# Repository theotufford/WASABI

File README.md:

# WASABI
WASABI stands for Well Applied Server Automated Biological Interface. Wasabi is a 5 bar linkage based pipetting robot that is automated via raspberry pi and the python flask library This page contains both the information and documentation for the software package as well as the mechanical assembly of the pipetting robot. The pipetting robot in this build is a slightly modified version of the [Phil pipetting robot](https://www.biorxiv.org/content/10.1101/2021.07.04.448641v1.full). Though the rpi and stepper breakout boards can be used with any machine and the wasabi machine config can be modified for any 5-bar based pipetting robot.  
## [Bill of Materials (BOM)](https://docs.google.com/spreadsheets/d/16TOlXRDoKtlOAvTiCGKz8jH9Rkvl1hXIs9z1LAUZMCc/edit?usp=sharing)

(currently working actively with this BOM but if you decide to build this project you should make your own copy and make sure to clear all of the material statuses and reset them to red so you can track)

## software outline
The core of Wasabi has three main goals:
1. intuitively program and store experiments through a visual interface 
2. run experiments and directly control the robot 

### diagram
[insert diagram here]

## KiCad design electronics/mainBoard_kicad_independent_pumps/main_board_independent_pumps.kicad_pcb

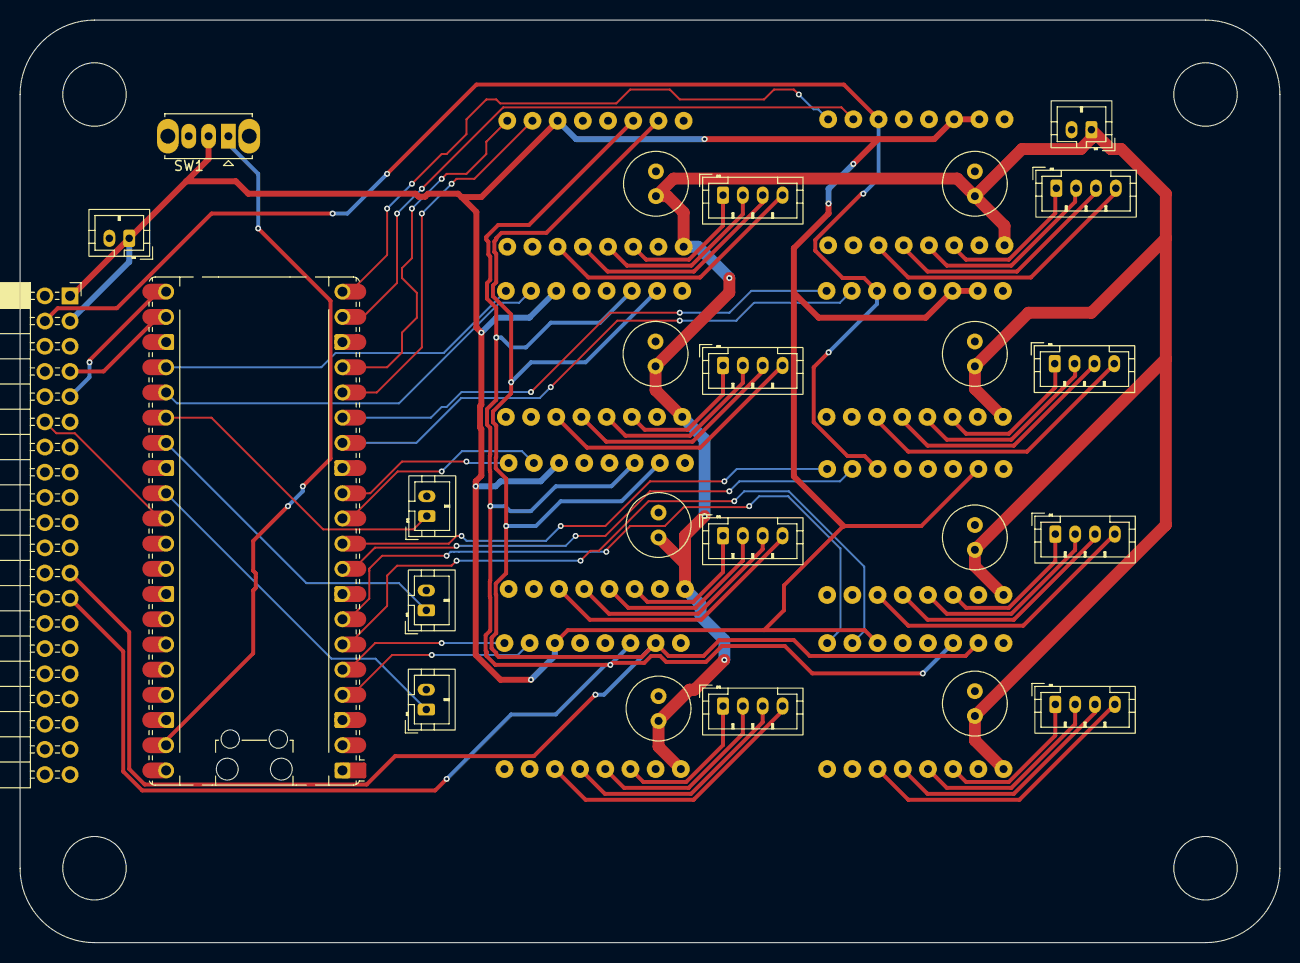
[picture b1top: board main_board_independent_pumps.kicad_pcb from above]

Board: 2 copper layers, 127.0 x 93.0 mm, 32 parts (0 on the bottom side), 61 nets.

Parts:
3b+header1: PinSocket_2x20_P2.54mm_Horizontal
A1: RaspberryPi_Pico; RaspberryPi_Pico_Common_Unspecified
A_mot1: mp6500
B_mot1: mp6500
C1, C2, C3, C4, C5, C6, C7, C8: C_Small_US; C_Radial_D6.3mm_H11.0mm_P2.50mm
J1: A_lim; JST_PH_B2B-PH-K_1x02_P2.00mm_Vertical
J2: B_lim; JST_PH_B2B-PH-K_1x02_P2.00mm_Vertical
J3: Z_lim; JST_PH_B2B-PH-K_1x02_P2.00mm_Vertical
J4, J5, J6, J7, J8, J9, J12, J13: Conn_01x04_Socket; JST_PH_B4B-PH-K_1x04_P2.00mm_Vertical
J10: 5v; JST_PH_B2B-PH-K_1x02_P2.00mm_Vertical
J11: 24v; JST_PH_B2B-PH-K_1x02_P2.00mm_Vertical
SW1: SW_DPDT_x2; SW_Slide_SPDT_Straight_CK_OS102011MS2Q
pump1, pump2, pump3, pump4, pump5: mp6500
z_mot1: mp6500

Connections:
+5V: 3b+header1.1 (5V), 3b+header1.3 (5V), A_mot1.2 (MS1), A_mot1.3 (MS2), B_mot1.2 (MS1), B_mot1.3 (MS2), J10.1, SW1.2 (B), pump1.6 (VLOG), pump2.6 (VLOG), pump3.6 (VLOG), pump4.6 (VLOG), pump5.6 (VLOG), z_mot1.2 (MS1)
+24V: A_mot1.9 (VMOT), B_mot1.9 (VMOT), C1.2, C2.2, C3.2, C4.2, C5.2, C6.2, C7.2, C8.2, J11.1, pump1.9 (VMOT), pump2.9 (VMOT), pump3.9 (VMOT), pump4.9 (VMOT), pump5.9 (VMOT), z_mot1.9 (VMOT)
/A_dir: A1.20 (GPIO15), A_mot1.8 (DIR)
/A_step: A1.19 (GPIO14), A_mot1.7 (STEP)
/B_dir: A1.15 (GPIO11), B_mot1.8 (DIR)
/B_step: A1.14 (GPIO10), B_mot1.7 (STEP)
/P_ms1: 3b+header1.23 (GPIO8), pump1.2 (MS1), pump2.2 (MS1), pump3.2 (MS1), pump4.2 (MS1), pump5.2 (MS1)
/P_ms2: 3b+header1.25 (GPIO7), pump1.3 (MS2), pump2.3 (MS2), pump3.3 (MS2), pump4.3 (MS2), pump5.3 (MS2)
/Pico_reset: 3b+header1.12 (GPIO17), A1.30 (RUN)
/enable: 3b+header1.4 (GPIO2), A_mot1.6 (VLOG), B_mot1.6 (VLOG), z_mot1.6 (VLOG)
/p1_dir: A1.7 (GPIO5), pump1.8 (DIR)
/p1_step: A1.6 (GPIO4), pump1.7 (STEP)
/p2_dir: A1.17 (GPIO13), pump2.8 (DIR)
/p2_step: A1.16 (GPIO12), pump2.7 (STEP)
/p3_dir: A1.24 (GPIO18), pump3.8 (DIR)
/p3_step: A1.25 (GPIO19), pump3.7 (STEP)
/p4_dir: A1.5 (GPIO3), pump4.8 (DIR)
/p4_step: A1.4 (GPIO2), pump4.7 (STEP)
/p5_dir: A1.12 (GPIO9), pump5.8 (DIR)
/p5_step: A1.11 (GPIO8), pump5.7 (STEP)
/uart_RX: 3b+header1.9 (GPIO15), A1.21 (GPIO16)
/uart_TX: 3b+header1.7 (GPIO14), A1.22 (GPIO17)
/z_dir: A1.10 (GPIO7), z_mot1.8 (DIR)
/z_step: A1.9 (GPIO6), z_mot1.7 (STEP)
GND: 3b+header1.5 (GND), 3b+header1.10 (GND), 3b+header1.13 (GND), 3b+header1.19 (GND), 3b+header1.26 (GND), 3b+header1.33 (GND), 3b+header1.40 (GND), A1.3 (GND), A1.8 (GND), A1.13 (GND), A1.18 (GND), A1.23 (GND), A1.28 (GND), A1.33 (AGND), A1.38 (GND), A_mot1.10 (GND), A_mot1.16 (LGND), B_mot1.10 (GND), B_mot1.16 (LGND), C1.1, C2.1, C3.1, C4.1, C5.1, C6.1, C7.1, C8.1, J1.2, J2.2, J3.2, J10.2, J11.2, pump1.10 (GND), pump1.16 (LGND), pump2.10 (GND), pump2.16 (LGND), pump3.10 (GND), pump3.16 (LGND), pump4.10 (GND), pump4.16 (LGND), pump5.10 (GND), pump5.16 (LGND), z_mot1.10 (GND), z_mot1.16 (LGND)
unnamed: A1.26 (GPIO20), J3.1
unnamed: A1.27 (GPIO21), J2.1
unnamed: A1.29 (GPIO22), J1.1
unnamed: A1.39 (VSYS), SW1.1 (A)
unnamed: A_mot1.13 (A1), J4.3
unnamed: A_mot1.14 (A2), J4.4
unnamed: A_mot1.12 (B1), J4.2
unnamed: A_mot1.11 (B2), J4.1
unnamed: B_mot1.13 (A1), J5.3
unnamed: B_mot1.14 (A2), J5.4
unnamed: B_mot1.12 (B1), J5.2
unnamed: B_mot1.11 (B2), J5.1
unnamed: J6.1, z_mot1.11 (B2)
unnamed: J6.2, z_mot1.12 (B1)
unnamed: J6.3, z_mot1.13 (A1)
unnamed: J6.4, z_mot1.14 (A2)
unnamed: J7.1, pump3.11 (B2)
unnamed: J7.2, pump3.12 (B1)
unnamed: J7.3, pump3.13 (A1)
unnamed: J7.4, pump3.14 (A2)
unnamed: J8.1, pump2.11 (B2)
unnamed: J8.2, pump2.12 (B1)
unnamed: J8.3, pump2.13 (A1)
unnamed: J8.4, pump2.14 (A2)
unnamed: J9.1, pump1.11 (B2)
unnamed: J9.2, pump1.12 (B1)
unnamed: J9.3, pump1.13 (A1)
unnamed: J9.4, pump1.14 (A2)
unnamed: J12.1, pump4.11 (B2)
unnamed: J12.2, pump4.12 (B1)
unnamed: J12.3, pump4.13 (A1)
unnamed: J12.4, pump4.14 (A2)
unnamed: J13.1, pump5.11 (B2)
unnamed: J13.2, pump5.12 (B1)
unnamed: J13.3, pump5.13 (A1)
unnamed: J13.4, pump5.14 (A2)

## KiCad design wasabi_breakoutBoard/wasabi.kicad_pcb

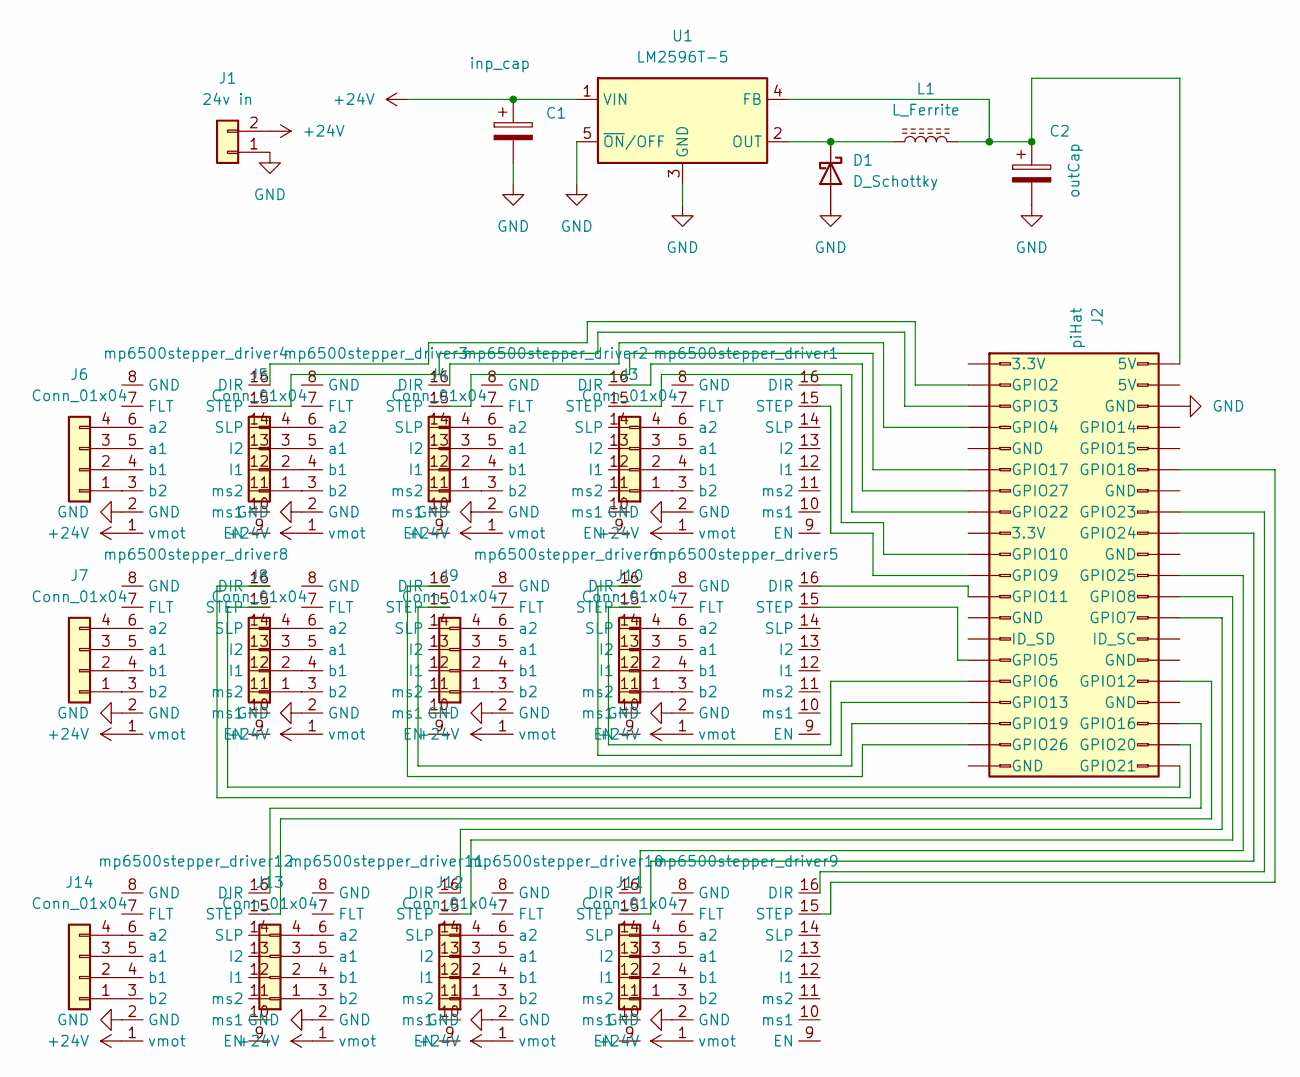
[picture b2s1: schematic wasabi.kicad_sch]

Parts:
C1: inp_cap; C_Radial_D10.0mm_H20.0mm_P5.00mm
C2: outCap; CP_Radial_D8.0mm_P3.50mm
D1: D_Schottky; D_DO-201AD_P15.24mm_Horizontal
J1: 24v in; JST_XH_B2B-XH-A_1x02_P2.50mm_Vertical
J2: piHat; PinHeader_2x20_P2.54mm_Vertical
J3, J4, J5, J6, J7, J8, J9, J10, J11, J12, J13, J14: Conn_01x04; JST_XH_B4B-XH-A_1x04_P2.50mm_Vertical
L1: L_Ferrite; L_Coilcraft_MSS1278-XXX
U1: LM2596T-5; TO-220-5_P3.4x3.7mm_StaggerOdd_Lead3.8mm_Vertical
mp6500stepper_driver1, mp6500stepper_driver2, mp6500stepper_driver3, mp6500stepper_driver4, mp6500stepper_driver5, mp6500stepper_driver6, mp6500stepper_driver7, mp6500stepper_driver8, mp6500stepper_driver9, mp6500stepper_driver10, mp6500stepper_driver11, mp6500stepper_driver12: mp6500

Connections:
+24V: C1.1, J1.2, U1.1 (VIN), mp6500stepper_driver1.1 (vmot), mp6500stepper_driver2.1 (vmot), mp6500stepper_driver3.1 (vmot), mp6500stepper_driver4.1 (vmot), mp6500stepper_driver5.1 (vmot), mp6500stepper_driver6.1 (vmot), mp6500stepper_driver7.1 (vmot), mp6500stepper_driver8.1 (vmot), mp6500stepper_driver9.1 (vmot), mp6500stepper_driver10.1 (vmot), mp6500stepper_driver11.1 (vmot), mp6500stepper_driver12.1 (vmot)
GND: C1.2, C2.2, D1.2 (A), J1.1, J2.6 (GND), U1.3 (GND), U1.5 (~ON/OFF), mp6500stepper_driver1.2 (GND), mp6500stepper_driver2.2 (GND), mp6500stepper_driver3.2 (GND), mp6500stepper_driver4.2 (GND), mp6500stepper_driver5.2 (GND), mp6500stepper_driver6.2 (GND), mp6500stepper_driver7.2 (GND), mp6500stepper_driver8.2 (GND), mp6500stepper_driver9.2 (GND), mp6500stepper_driver10.2 (GND), mp6500stepper_driver11.2 (GND), mp6500stepper_driver12.2 (GND)
unnamed: D1.1 (K), L1.1, U1.2 (OUT)
unnamed: J2.3 (GPIO2), mp6500stepper_driver4.16 (DIR)
unnamed: J2.5 (GPIO3), mp6500stepper_driver4.15 (STEP)
unnamed: J2.7 (GPIO4), mp6500stepper_driver3.16 (DIR)
unnamed: J2.29 (GPIO5), mp6500stepper_driver5.15 (STEP)
unnamed: J2.31 (GPIO6), mp6500stepper_driver6.15 (STEP)
unnamed: J2.26 (GPIO7), mp6500stepper_driver11.16 (DIR)
unnamed: J2.24 (GPIO8), mp6500stepper_driver11.15 (STEP)
unnamed: J2.21 (GPIO9), mp6500stepper_driver1.15 (STEP)
unnamed: J2.19 (GPIO10), mp6500stepper_driver1.16 (DIR)
unnamed: J2.23 (GPIO11), mp6500stepper_driver5.16 (DIR)
unnamed: J2.32 (GPIO12), mp6500stepper_driver12.15 (STEP)
unnamed: J2.33 (GPIO13), mp6500stepper_driver6.16 (DIR)
unnamed: J2.36 (GPIO16), mp6500stepper_driver12.16 (DIR)
unnamed: J2.11 (GPIO17), mp6500stepper_driver3.15 (STEP)
unnamed: J2.12 (GPIO18), mp6500stepper_driver9.15 (STEP)
unnamed: J2.35 (GPIO19), mp6500stepper_driver7.15 (STEP)
unnamed: J2.38 (GPIO20), mp6500stepper_driver8.16 (DIR)
unnamed: J2.40 (GPIO21), mp6500stepper_driver8.15 (STEP)
unnamed: J2.15 (GPIO22), mp6500stepper_driver2.15 (STEP)
unnamed: J2.16 (GPIO23), mp6500stepper_driver9.16 (DIR)
unnamed: J2.18 (GPIO24), mp6500stepper_driver10.15 (STEP)
unnamed: J2.22 (GPIO25), mp6500stepper_driver10.16 (DIR)
unnamed: J2.37 (GPIO26), mp6500stepper_driver7.16 (DIR)
unnamed: J2.13 (GPIO27), mp6500stepper_driver2.16 (DIR)
unnamed: J3.1, mp6500stepper_driver1.3 (b2)
unnamed: J3.2, mp6500stepper_driver1.4 (b1)
unnamed: J3.3, mp6500stepper_driver1.5 (a1)
unnamed: J3.4, mp6500stepper_driver1.6 (a2)
unnamed: J4.1, mp6500stepper_driver2.3 (b2)
unnamed: J4.2, mp6500stepper_driver2.4 (b1)
unnamed: J4.3, mp6500stepper_driver2.5 (a1)
unnamed: J4.4, mp6500stepper_driver2.6 (a2)
unnamed: J5.1, mp6500stepper_driver3.3 (b2)
unnamed: J5.2, mp6500stepper_driver3.4 (b1)
unnamed: J5.3, mp6500stepper_driver3.5 (a1)
unnamed: J5.4, mp6500stepper_driver3.6 (a2)
unnamed: J6.1, mp6500stepper_driver4.3 (b2)
unnamed: J6.2, mp6500stepper_driver4.4 (b1)
unnamed: J6.3, mp6500stepper_driver4.5 (a1)
unnamed: J6.4, mp6500stepper_driver4.6 (a2)
unnamed: J7.1, mp6500stepper_driver8.3 (b2)
unnamed: J7.2, mp6500stepper_driver8.4 (b1)
unnamed: J7.3, mp6500stepper_driver8.5 (a1)
unnamed: J7.4, mp6500stepper_driver8.6 (a2)
unnamed: J8.1, mp6500stepper_driver7.3 (b2)
unnamed: J8.2, mp6500stepper_driver7.4 (b1)
unnamed: J8.3, mp6500stepper_driver7.5 (a1)
unnamed: J8.4, mp6500stepper_driver7.6 (a2)
unnamed: J9.1, mp6500stepper_driver6.3 (b2)
unnamed: J9.2, mp6500stepper_driver6.4 (b1)
unnamed: J9.3, mp6500stepper_driver6.5 (a1)
unnamed: J9.4, mp6500stepper_driver6.6 (a2)
unnamed: J10.1, mp6500stepper_driver5.3 (b2)
unnamed: J10.2, mp6500stepper_driver5.4 (b1)
unnamed: J10.3, mp6500stepper_driver5.5 (a1)
unnamed: J10.4, mp6500stepper_driver5.6 (a2)
unnamed: J11.1, mp6500stepper_driver9.3 (b2)
unnamed: J11.2, mp6500stepper_driver9.4 (b1)
unnamed: J11.3, mp6500stepper_driver9.5 (a1)
unnamed: J11.4, mp6500stepper_driver9.6 (a2)
unnamed: J12.1, mp6500stepper_driver10.3 (b2)
unnamed: J12.2, mp6500stepper_driver10.4 (b1)
unnamed: J12.3, mp6500stepper_driver10.5 (a1)
unnamed: J12.4, mp6500stepper_driver10.6 (a2)
unnamed: J13.1, mp6500stepper_driver11.3 (b2)
unnamed: J13.2, mp6500stepper_driver11.4 (b1)
unnamed: J13.3, mp6500stepper_driver11.5 (a1)
unnamed: J13.4, mp6500stepper_driver11.6 (a2)
unnamed: J14.1, mp6500stepper_driver12.3 (b2)
unnamed: J14.2, mp6500stepper_driver12.4 (b1)
unnamed: J14.3, mp6500stepper_driver12.5 (a1)
unnamed: J14.4, mp6500stepper_driver12.6 (a2)
unnamed: C2.1, J2.2 (5V), L1.2, U1.4 (FB)

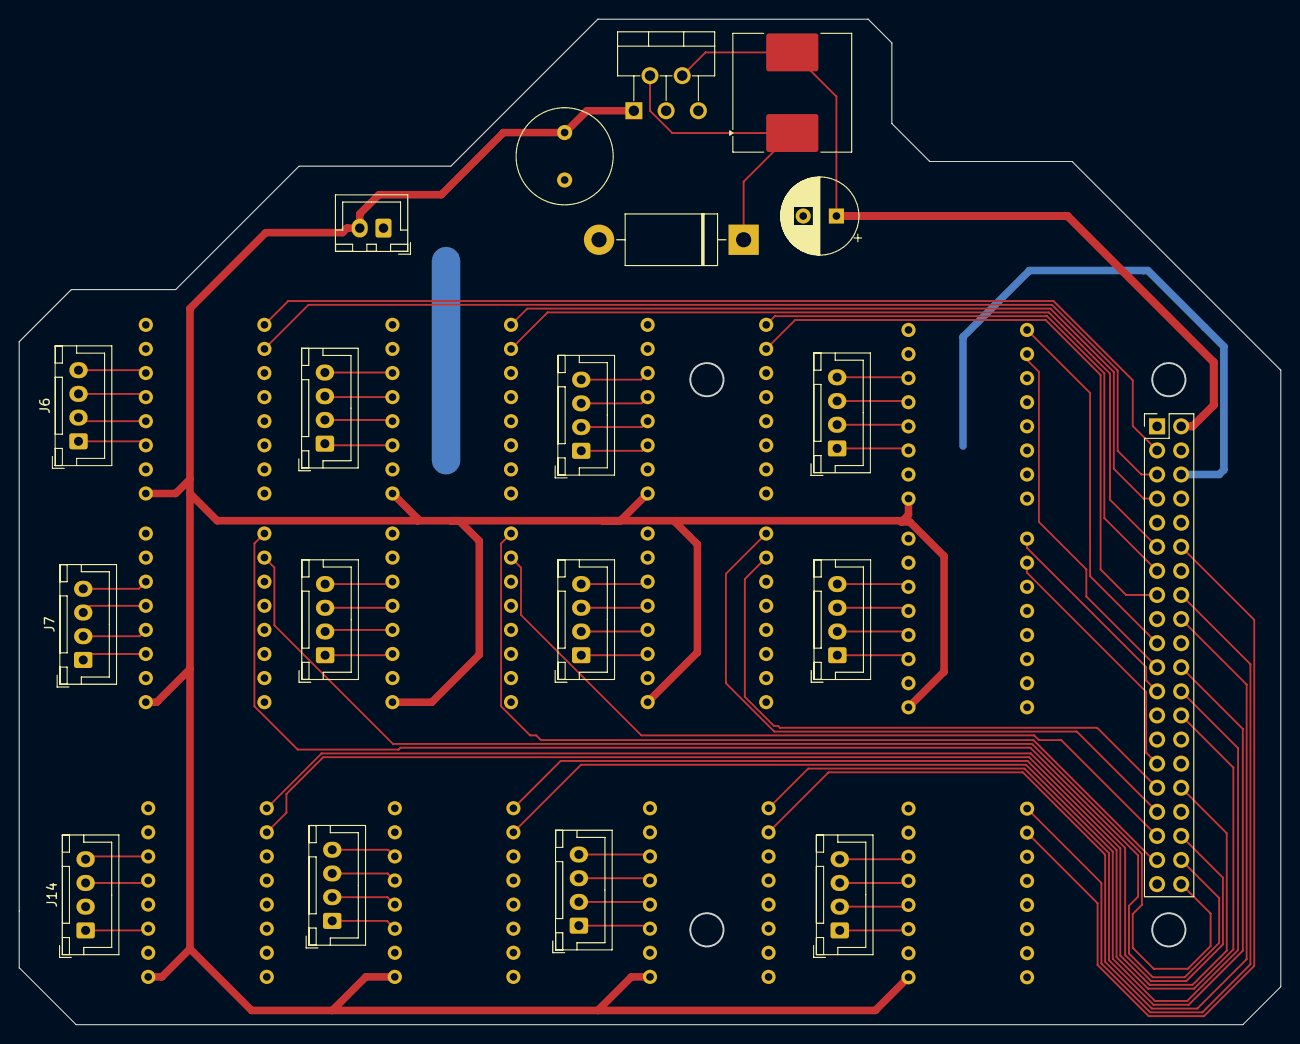
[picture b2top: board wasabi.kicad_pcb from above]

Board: 2 copper layers, 132.9 x 105.9 mm, 31 parts (0 on the bottom side), 76 nets.

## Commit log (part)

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2024-12-29 autosave is still broken asf, need to make it so logging an experiment over and over doesnt create duplicates and overwrites with version history, need to make the recover from experiment data functi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
2025-01-04 autosave is still the bane of my existence but I programmed most of the experiment slicer
2025-01-05 AHHHHHHHHHHH
2025-01-05 test
2025-01-05 fixed
2025-01-05 new!
2025-01-05 hope
2025-01-05 fixed massive icon lol
2025-02-08 first commit of the complete redo
2025-02-11 back to the terminal
2025-02-11 readme
2025-02-24 differential well coloring !!!!!
2025-03-19 big update, sorry its been a long time lol, finder functionality is working, color display is working, saving functionality is working, basically almost done with the programming interface, pretty sl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
2025-04-08 wasabi breakout board pcb
2025-04-09 final update before working on physical stuff
2025-05-21 updated PCBs
2025-05-22 working on translator in the test file in main
2025-05-23 end of week 1, translator mostly working, need db integration
2025-05-31 working motors with picols
2025-05-31 motors working!
2025-06-12 working on the motor controller
2025-06-26 updated board design
2025-06-26 motor controller working
2025-06-26 added untracked files
2025-06-27 modified ignore file and added search and log functionality to the material selector in the programmer forms
2025-06-27 removed venv for cleanliness
2025-06-27 trying to get rid of the weird python bulk
2025-07-07 fixed some visual bugs with the plate rendering as well as some other stuff I sort of forgot, gotta get into a better habit of pushing a commit at the end of every coding session so I can track chang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
2025-07-07 really buggy because of all the weird JSON handling, once this is all up and running I am gonna immediately try to re-write it all in react
2025-07-08 fixed bug where gradient methods wouldnt have their volume values loaded when they were rended
2025-07-31 in the process of porting to react, flask api somewhat unnaffected outside of json config
2025-08-05 trying to be better about committing daily, really just for the vain reason that I want my heatmap to be green lol
2025-08-06 modified file structure and started working on installer script
2025-08-08 removed depreciated flask frontend
2025-08-08 starting to rebuild api stuff
2025-08-08 sockets successfully exchange experiment object between back and frontend
2025-11-20 I dont even know but we are getting there
2025-11-20 added some ignored files?
2025-11-30 up to meeting
2025-12-01 prototype web serial monitor functioning with counter
2025-12-05 serial fixes
2026-01-05 starting redevelopment of machine controller this time in c++ and with a correctly structured library
2026-01-06 getting farther on library design, design notes out of date but only from this morning
2026-01-11 commit before i wipe a bunch of stuff to clean up
2026-01-11 simplified functions
2026-01-12 much more reliable serial
2026-01-14 laptop commit
2026-01-16 argument vector least working version completedgsgs
2026-01-26 working on implementing listener pins
2026-01-27 working integer reflection!!
2026-02-02 changed a lot of stuff in a rush and now im fixing everything
2026-02-04 finally working bug was in the fact i hardcoded every settings arg vec com to have the new pump code. oops.
2026-02-10 working settings initialization and reflection
2026-02-14 commirsntirsentiresnt
2026-02-15 working buzz function
    i need to stop doing the thing where i dont initialize my for loop index
    variable
2026-02-15 working absolute positioning with linear velocity
2026-03-18 split up files
    no more machine class, decided that entire functionality can be left to
    static variabless in the Motor class, as it sort of has to be anyways.
2026-04-16 added document describing some of the math behind accel timings
2026-05-27 fixed legend
2026-05-30 prelim author config
2026-06-15 some updates and lots of electronics stuff
2026-06-17 machine controller updates
2026-06-20 coms updates
2026-06-20 kinematics working
